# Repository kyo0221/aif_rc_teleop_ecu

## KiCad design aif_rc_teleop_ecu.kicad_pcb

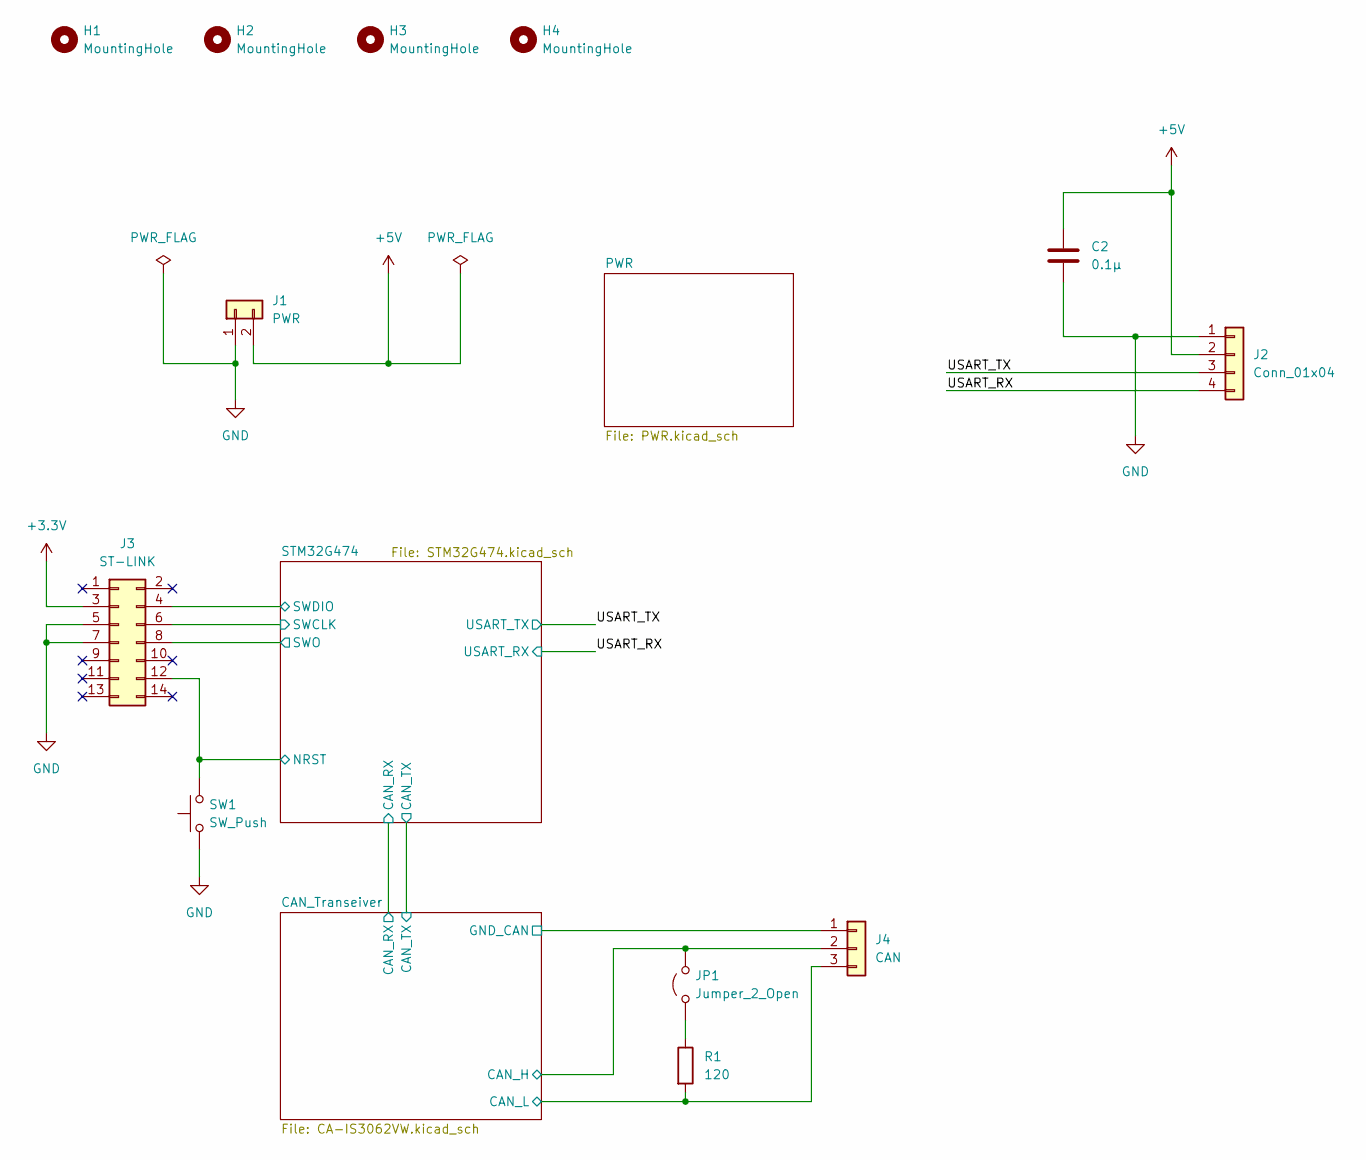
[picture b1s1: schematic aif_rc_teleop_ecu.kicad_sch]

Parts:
C2: 0.1μ; C_0603_1608Metric
H1, H2, H3, H4: MountingHole; MountingHole_3.2mm_M3
J1: PWR; JST_XA_B02B-XASK-1_1x02_P2.50mm_Vertical
J2: Conn_01x04; JST_XA_B04B-XASK-1_1x04_P2.50mm_Vertical
J3: ST-LINK; JTAG_BOX_CONN
J4: CAN; JST_XA_B03B-XASK-1_1x03_P2.50mm_Vertical
JP1: Jumper_2_Open; PinHeader_1x02_P2.54mm_Vertical
R1: 120; R_0603_1608Metric
SW1: SW_Push; SW_Push_1P1T_XKB_TS-1187A

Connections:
+3.3V: J3.3; also elsewhere on the board
+5V: C2.2, J1.2, J2.2; also elsewhere on the board
/CAN_Transeiver/CAN_H: J4.2, JP1.2 (B); also elsewhere on the board
/CAN_Transeiver/CAN_L: J4.3, R1.2; also elsewhere on the board
/CAN_Transeiver/GND_CAN: J4.1; also elsewhere on the board
/STM32G474/NRST: J3.12, SW1.2; also elsewhere on the board
/STM32G474/SWCLK: J3.6; also elsewhere on the board
/STM32G474/SWDIO: J3.4; also elsewhere on the board
/STM32G474/SWO: J3.8; also elsewhere on the board
/USART_RX: J2.4; also elsewhere on the board
/USART_TX: J2.3; also elsewhere on the board
GND: C2.1, J1.1, J2.1, J3.5, J3.7, SW1.1; also elsewhere on the board
unnamed: JP1.1 (A), R1.1

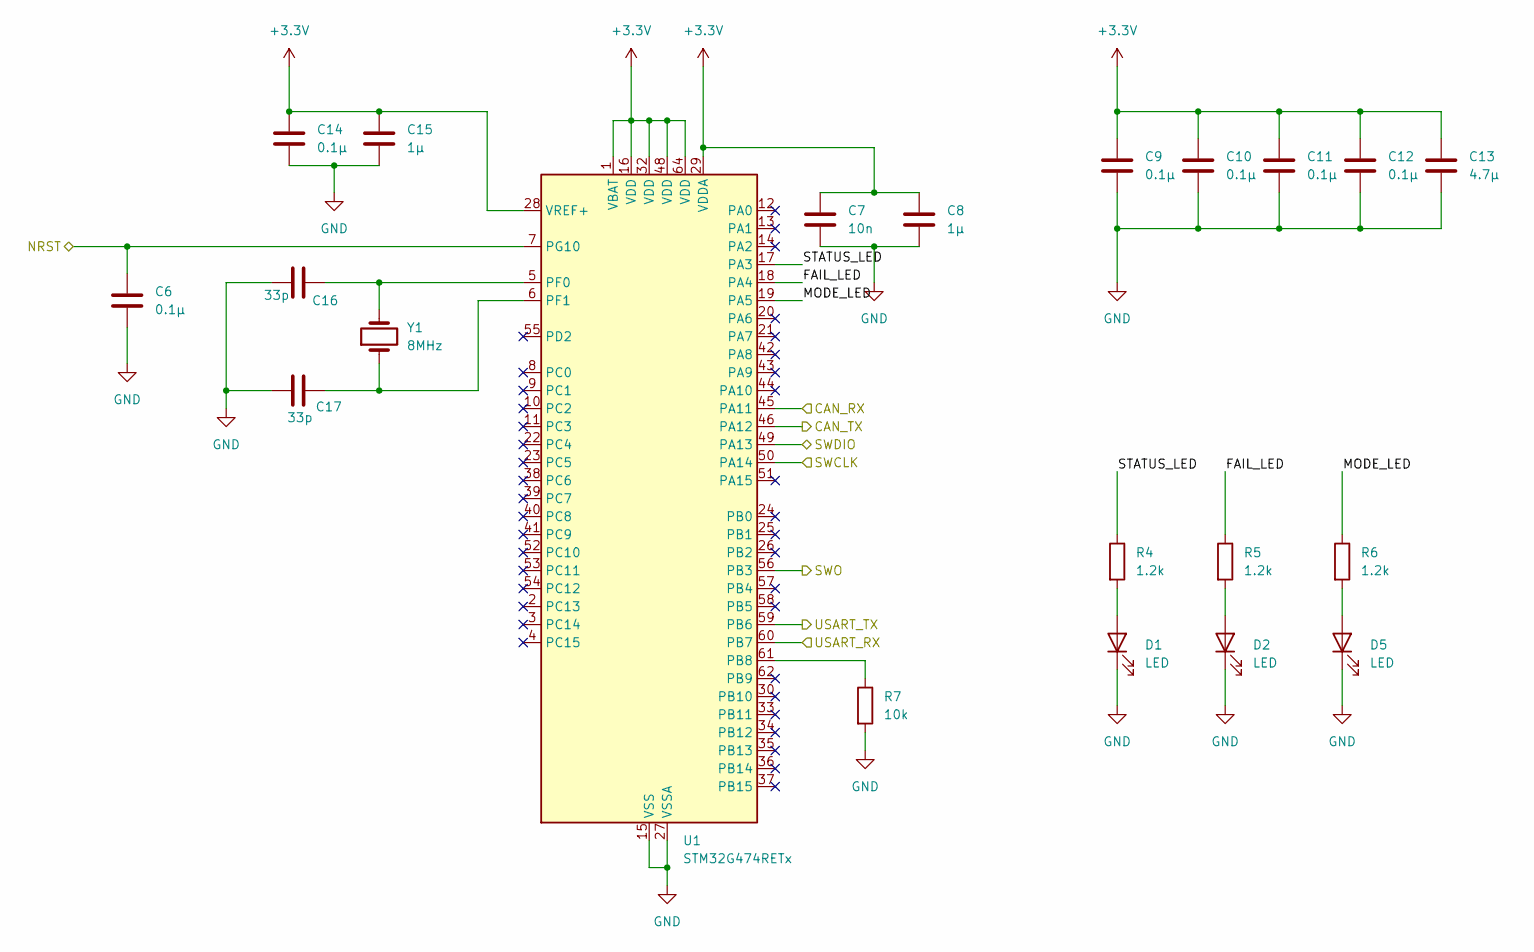
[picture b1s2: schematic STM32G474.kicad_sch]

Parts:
C6, C9, C10, C11, C12, C14: 0.1μ; C_0603_1608Metric
C7: 10n; C_0603_1608Metric
C8, C15: 1μ; C_0603_1608Metric
C13: 4.7μ; C_0603_1608Metric
C16, C17: 33p; C_0603_1608Metric
D1, D2, D5: LED; LED_0603_1608Metric
R4, R5, R6: 1.2k; R_0603_1608Metric
R7: 10k; R_0603_1608Metric
U1: STM32G474RETx; LQFP-64_10x10mm_P0.5mm
Y1: 8MHz; Crystal_SMD_5032-2Pin_5.0x3.2mm

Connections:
+3.3V: C7.1, C8.1, C9.1, C10.1, C11.1, C12.1, C13.1, C14.1, C15.1, U1.1 (VBAT), U1.16 (VDD), U1.28 (VREF+), U1.29 (VDDA), U1.32 (VDD), U1.48 (VDD), U1.64 (VDD); also elsewhere on the board
/CAN_Transeiver/CAN_RX: U1.45 (PA11); also elsewhere on the board
/CAN_Transeiver/CAN_TX: U1.46 (PA12); also elsewhere on the board
/STM32G474/FAIL_LED: R5.1, U1.18 (PA4)
/STM32G474/MODE_LED: R6.1, U1.19 (PA5)
/STM32G474/NRST: C6.1, U1.7 (PG10); also elsewhere on the board
/STM32G474/STATUS_LED: R4.1, U1.17 (PA3)
/STM32G474/SWCLK: U1.50 (PA14); also elsewhere on the board
/STM32G474/SWDIO: U1.49 (PA13); also elsewhere on the board
/STM32G474/SWO: U1.56 (PB3); also elsewhere on the board
/USART_RX: U1.60 (PB7); also elsewhere on the board
/USART_TX: U1.59 (PB6); also elsewhere on the board
GND: C6.2, C7.2, C8.2, C9.2, C10.2, C11.2, C12.2, C13.2, C14.2, C15.2, C16.1, C17.1, D1.1 (K), D2.1 (K), D5.1 (K), R7.2, U1.15 (VSS), U1.27 (VSSA), U1.31 (VSS), U1.47 (VSS), U1.63 (VSS); also elsewhere on the board
unnamed: D1.2 (A), R4.2
unnamed: D2.2 (A), R5.2
unnamed: D5.2 (A), R6.2
unnamed: R7.1, U1.61 (PB8)
unnamed: C16.2, U1.5 (PF0), Y1.2
unnamed: C17.2, U1.6 (PF1), Y1.1

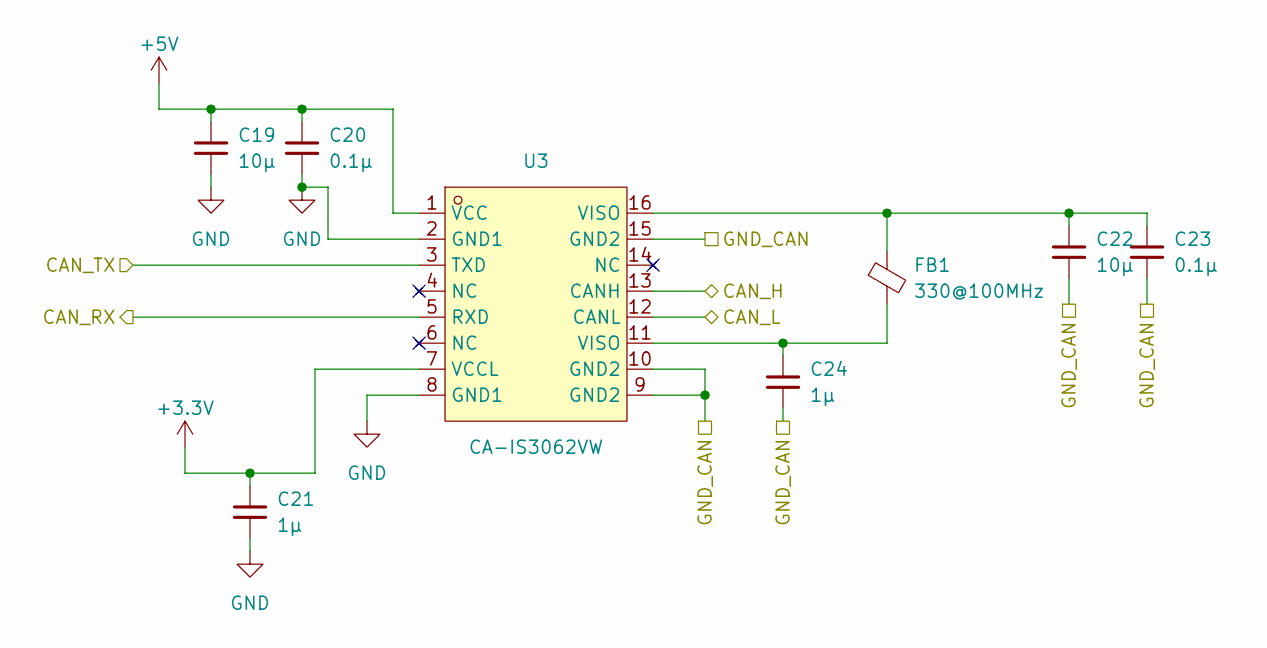
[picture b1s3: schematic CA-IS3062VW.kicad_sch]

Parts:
C19, C22: 10μ; C_0805_2012Metric; LCSC C15850
C20, C23: 0.1μ; C_0603_1608Metric; LCSC C14663
C21, C24: 1μ; C_0603_1608Metric; LCSC C15849
FB1: 330@100MHz; L_0402_1005Metric; MPN BLM15EX331SN1D; LCSC C596498
U3: CA-IS3062VW; SOIC-16W_7.5x10.3mm_P1.27mm; MPN CA-IS3062VW; LCSC C5338808

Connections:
+3.3V: C21.1, U3.7 (VCCL); also elsewhere on the board
+5V: C19.1, C20.1, U3.1 (VCC); also elsewhere on the board
/CAN_Transeiver/CAN_H: U3.13 (CANH); also elsewhere on the board
/CAN_Transeiver/CAN_L: U3.12 (CANL); also elsewhere on the board
/CAN_Transeiver/CAN_RX: U3.5 (RXD); also elsewhere on the board
/CAN_Transeiver/CAN_TX: U3.3 (TXD); also elsewhere on the board
/CAN_Transeiver/GND_CAN: C22.2, C23.2, C24.2, U3.9 (GND2), U3.10 (GND2), U3.15 (GND2); also elsewhere on the board
GND: C19.2, C20.2, C21.2, U3.2 (GND1), U3.8 (GND1); also elsewhere on the board
unnamed: C22.1, C23.1, FB1.1, U3.16 (VISO)
unnamed: C24.1, FB1.2, U3.11 (VISO)

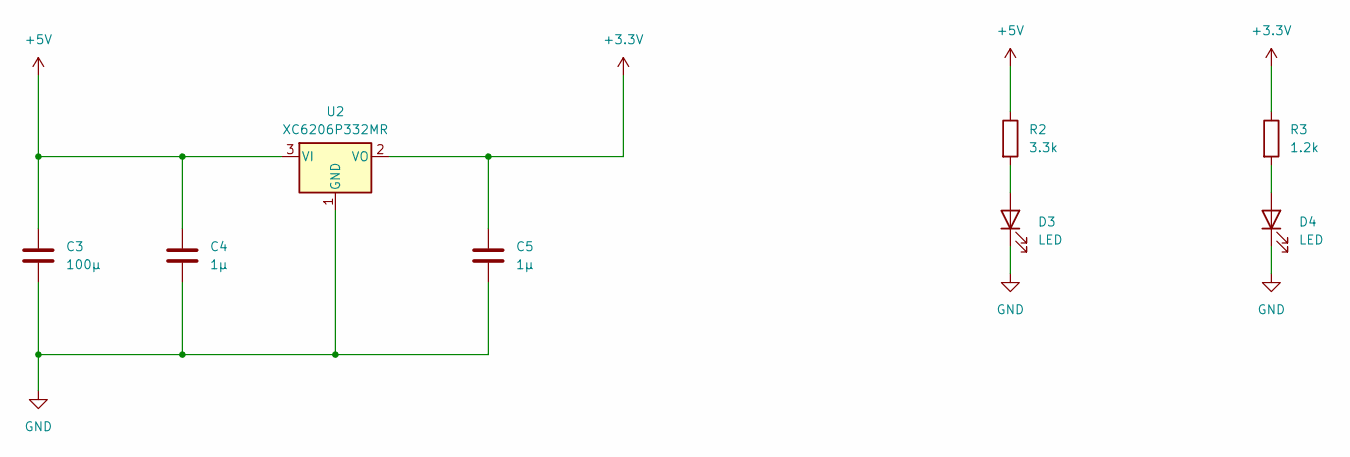
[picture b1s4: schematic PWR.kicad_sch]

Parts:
C3: 100μ; CP_Radial_D6.3mm_P2.50mm
C4, C5: 1μ; C_0603_1608Metric
D3, D4: LED; LED_0603_1608Metric
R2: 3.3k; R_0603_1608Metric
R3: 1.2k; R_0603_1608Metric
U2: XC6206P332MR; SOT-23-3

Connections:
+3.3V: C5.1, R3.1, U2.2 (VO); also elsewhere on the board
+5V: C3.1, C4.1, R2.1, U2.3 (VI); also elsewhere on the board
GND: C3.2, C4.2, C5.2, D3.1 (K), D4.1 (K), U2.1 (GND); also elsewhere on the board
unnamed: D3.2 (A), R2.2
unnamed: D4.2 (A), R3.2

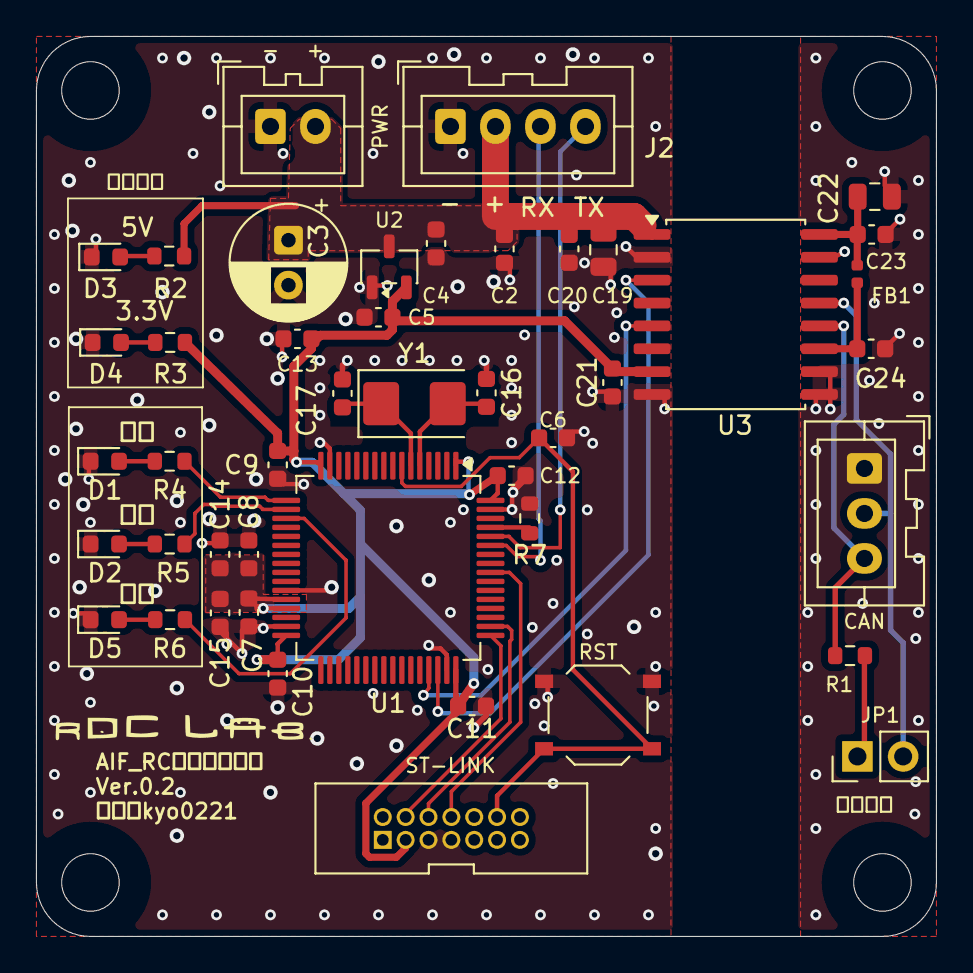
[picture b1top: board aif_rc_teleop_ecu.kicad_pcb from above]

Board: 2 copper layers, 50.0 x 50.0 mm, 49 parts (0 on the bottom side), 28 nets.

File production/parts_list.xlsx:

製作枚数 | 5 | ← 黄色セルを変えると数量・小計が再計算されます（Economic PCBA で実装する表面実装部品。単価・在庫はJLC API 2026-11-09取得）
No | Ref | 値 | パッケージ | LCSC番号 | メーカー型番 | 区分 | 1枚あたり数量 | 必要数 | 単価(USD) | 小計(USD) | 状態 | 備考
1 | C2,C6,C9,C10,C11,C12,C14,C20,C23 | 100nF 50V X7R ±10% | 0603 | C14663 | CC0603KRX7R9BB104 | Basic | 9 |  | 0.006 |  | 確認済 2026-11-09 | バイパス/デカップリング JLC在庫 32,993,629（2026-11-09）
2 | C4,C5,C8,C15,C21,C24 | 1µF 50V X5R ±10% | 0603 | C15849 | CL10A105KB8NNNC | Basic | 6 |  | 0.0109 |  | 確認済 2026-11-09 | JLC在庫 12,623,126（2026-11-09）
3 | C7 | 10nF 50V X7R ±10% | 0603 | C57112 | 0603B103K500NT | Basic | 1 |  | 0.0103 |  | 確認済 2026-11-09 | JLC在庫 5,750,512（2026-11-09）
4 | C13 | 4.7µF 16V X5R ±10% | 0603 | C19666 | CL10A475KO8NNNC | Basic | 1 |  | 0.015 |  | 確認済 2026-11-09 | C13 JLC在庫 3,723,176（2026-11-09）
5 | C16,C17 | 33pF 50V C0G ±5% | 0603 | C1663 | CL10C330JB8NNNC | Basic | 2 |  | 0.0091 |  | 確認済 2026-11-09 | Y1(CL=20pF)用。33pF直列16.5pF+浮遊容量で適合 JLC在庫 1,421,873（2026-11-09）
6 | C19,C22 | 10µF 25V X5R ±10% | 0805 | C15850 | CL21A106KAYNNNE | Basic | 2 |  | 0.0315 |  | 確認済 2026-11-09 | C19/C22 JLC在庫 8,362,759（2026-11-09）
7 | D1 | LED 黄緑 Vf2.0-2.2V 30-42mcd | 0603 | C2289 | KT-0603YG | Extended | 1 |  | 0.0106 |  | 確認済 2026-11-09 | D1=状態。色決定済み(黄緑)。暗さは実機確認 JLC在庫 36,894（2026-11-09）
8 | D2,D3,D4 | LED 赤 Vf1.8-2.4V | 0603 | C2286 | KT-0603R | Basic | 3 |  | 0.0077 |  | 確認済 2026-11-09 | D2=異常 D3=5V表示 D4=3.3V表示。色決定済み(赤)。暗さは実機確認 JLC在庫 6,497,473（2026-11-09）
9 | D5 | LED 黄 Vf2.4V 175mcd | 0603 | C2287 | KT-0603Y | Extended | 1 |  | 0.0106 |  | 確認済 2026-11-09 | D5=モード。色決定済み(黄)。暗さは実機確認 JLC在庫 86,988（2026-11-09）
10 | FB1 | 330Ω@100MHz 700mA | 0402 | C596498 | BLM15EX331SN1D | Extended | 1 |  | 0.08989999999999999 |  | 確認済 2026-11-09 | FB1 JLC在庫 36,595（2026-11-09）
11 | R1 | 120Ω ±1% | 0603 | C22787 | 0603WAF1200T5E | Basic | 1 |  | 0.002 |  | 確認済 2026-11-09 | CAN終端 JLC在庫 2,693,768（2026-11-09）
12 | R2 | 3.3kΩ ±1% | 0603 | C22978 | 0603WAF3301T5E | Basic | 1 |  | 0.0022 |  | 確認済 2026-11-09 | 5V表示LED(D3) JLC在庫 4,761,882（2026-11-09）
13 | R3,R4,R5,R6 | 1.2kΩ ±1% | 0603 | C22765 | 0603WAF1201T5E | Basic | 4 |  | 0.0034 |  | 確認済 2026-11-09 | LED電流制限(D1,D2,D4,D5) JLC在庫 2,156,026（2026-11-09）
14 | R7 | 10kΩ ±1% | 0603 | C25804 | 0603WAF1002T5E | Basic | 1 |  | 0.0022 |  | 確認済 2026-11-09 | BOOT0プルダウン JLC在庫 46,759,857（2026-11-09）
15 | SW1 | タクトスイッチ SMD-4P 5.1×5.1 | SMD 5.1x5.1 | C318884 | TS-1187A-B-A-B | Basic | 1 |  | 0.0207 |  | 確認済 2026-11-09 | リセットSW。接点ペア要確認(要確認シート) JLC在庫 844,638（2026-11-09）
16 | U1 | STM32G474RET6 | LQFP-64 | C521608 | STM32G474RET6 | Extended | 1 |  | 13.0055 |  | 確認済 2026-11-09 | JLC在庫 153個（2026-11-09時点）。少量のため発注直前に再確認
17 | U2 | XC6206P332MR 3.3V LDO | SOT-23-3 | C5446 | XC6206P332MR-G | Basic | 1 |  | 0.1478 |  | 確認済 2026-11-09 | 入力最大6V JLC在庫 490,069（2026-11-09）
18 | U3 | CA-IS3062VW 絶縁CAN(電源内蔵) | SOIC-16W | C5338808 | CA-IS3062VW | Extended | 1 |  | 3.0163 |  | 確認済 2026-11-09 | JLC在庫 3,809個（2026-11-09時点）
19 | Y1 | 8MHz 20pF ±10ppm | 5032 2P | C115962 | X50328MSB2GI | Basic | 1 |  | 0.2461 |  | 確認済 2026-11-09 | X50328MSB2GI JLC在庫 498,737（2026-11-09）
 |  |  |  |  |  |  |  |  | 部品代合計
 |  |  |  |  |  |  |  |  | 拡張部品の品種数
 |  |  |  |  |  |  |  |  | 拡張部品手数料(目安$3/品種)
